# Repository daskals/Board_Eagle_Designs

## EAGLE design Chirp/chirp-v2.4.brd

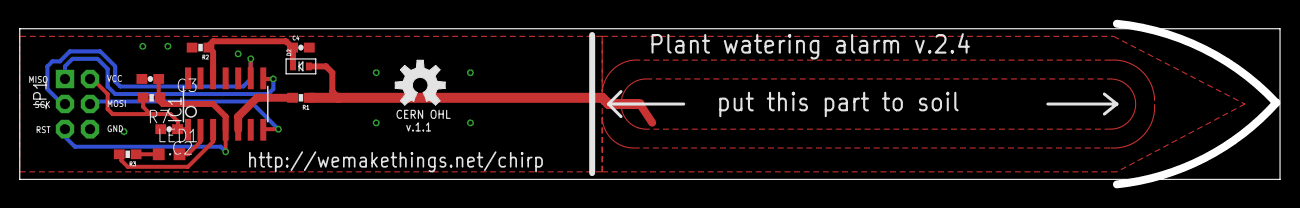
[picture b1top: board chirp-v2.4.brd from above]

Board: 2 copper layers, 127.5 x 16.3 mm, 11 parts (0 on the bottom side), 12 nets.

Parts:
C2, C3: 100nF; 0603-CAP
C4: 1uF; 0603-CAP
D2: DIODE-SCHOTTKY_; SOD-523
IC1: TINY24/44/84-SSU; SOIC14
JP1: AVR_SPI_PRG_6NS; 2X3-NS
LED1: CHIPLED_0805
R1, R7: 10K; 0603-RES
R2: 510K; 0603-RES
R3: 100R; 0603-RES

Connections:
CAPACITANCE_V: C4.1, D2.K, IC1.12, R2.1
CLK_OUT: IC1.5, R1.2
GND: C2.2, C3.2, C4.2, IC1.14, JP1.6, R2.2
LED_A: IC1.3, R3.2
LED_K: IC1.2, LED1.C
MISO: IC1.8, JP1.1
MOSI: IC1.7, JP1.4
unnamed: LED1.A, R3.1
RESET: C3.1, IC1.4, JP1.5, R7.1
SCK: IC1.9, JP1.3
VCC: C2.1, IC1.1, JP1.2, R7.2
V_CAP: D2.A, R1.1

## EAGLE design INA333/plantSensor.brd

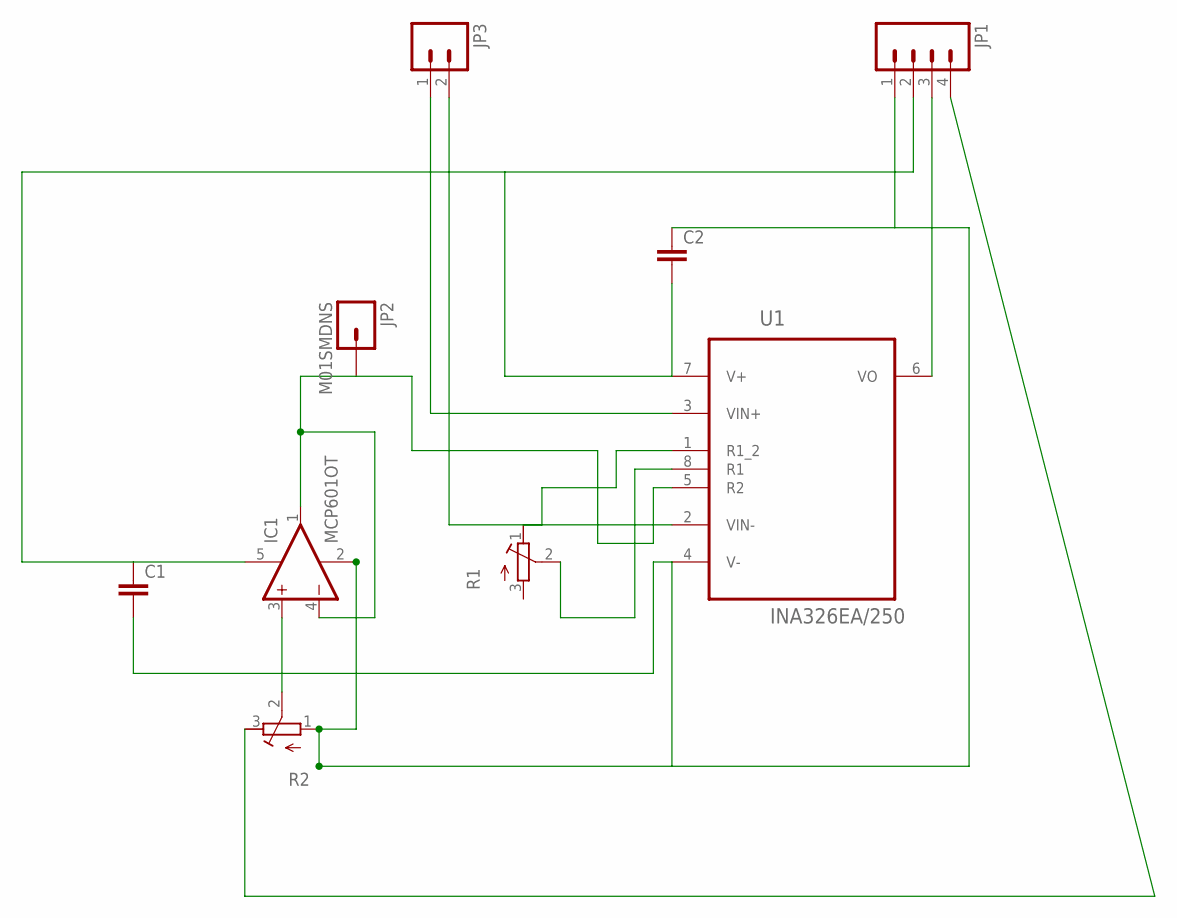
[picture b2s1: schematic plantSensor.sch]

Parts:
C1, C2: C2.5/4; C2.5-4
IC1: MCP601OT; SOT23-5
JP1: M04PTH; 1X04
JP2: M01SMDNS; 1X01NS
JP3: M02PTH; 1X02
R1: R-TRIMM3314G; RTRIM3314G
R2: R-TRIMM3314J; RTRIM3314J
U1: INA326EA/250; SOP65P490X110-8N

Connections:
AA: C1.1, C2.2, IC1.5 (V+), JP1.2, U1.7 (V+)
GND: C1.2, C2.1, IC1.2 (V-), JP1.1, R2.1 (E), U1.4 (V-)
unnamed: JP1.3, U1.6 (VO)
unnamed: IC1.3 (+IN), R2.2 (S)
unnamed: JP3.2, U1.2 (VIN-)
unnamed: JP3.1, U1.3 (VIN+)
unnamed: R1.2 (S), U1.8 (R1)
unnamed: R1.1 (E), U1.1 (R1_2)
unnamed: JP1.4, R2.3 (A)
unnamed: IC1.1 (OUT), IC1.4 (-IN), JP2.1, U1.5 (R2)

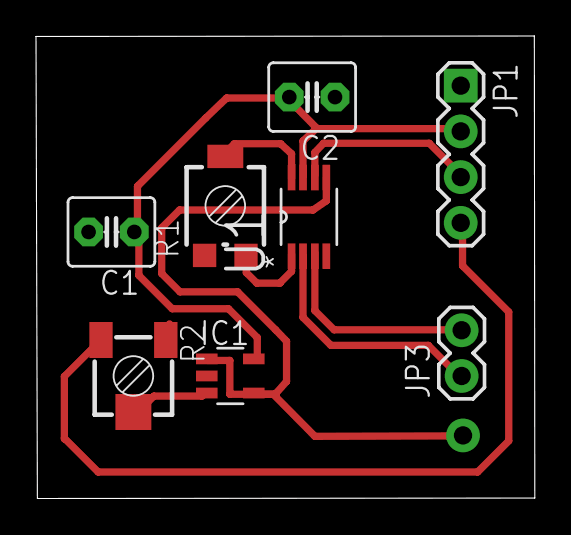
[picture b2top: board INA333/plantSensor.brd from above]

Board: 2 copper layers, 27.7 x 25.7 mm, 9 parts (0 on the bottom side), 10 nets.

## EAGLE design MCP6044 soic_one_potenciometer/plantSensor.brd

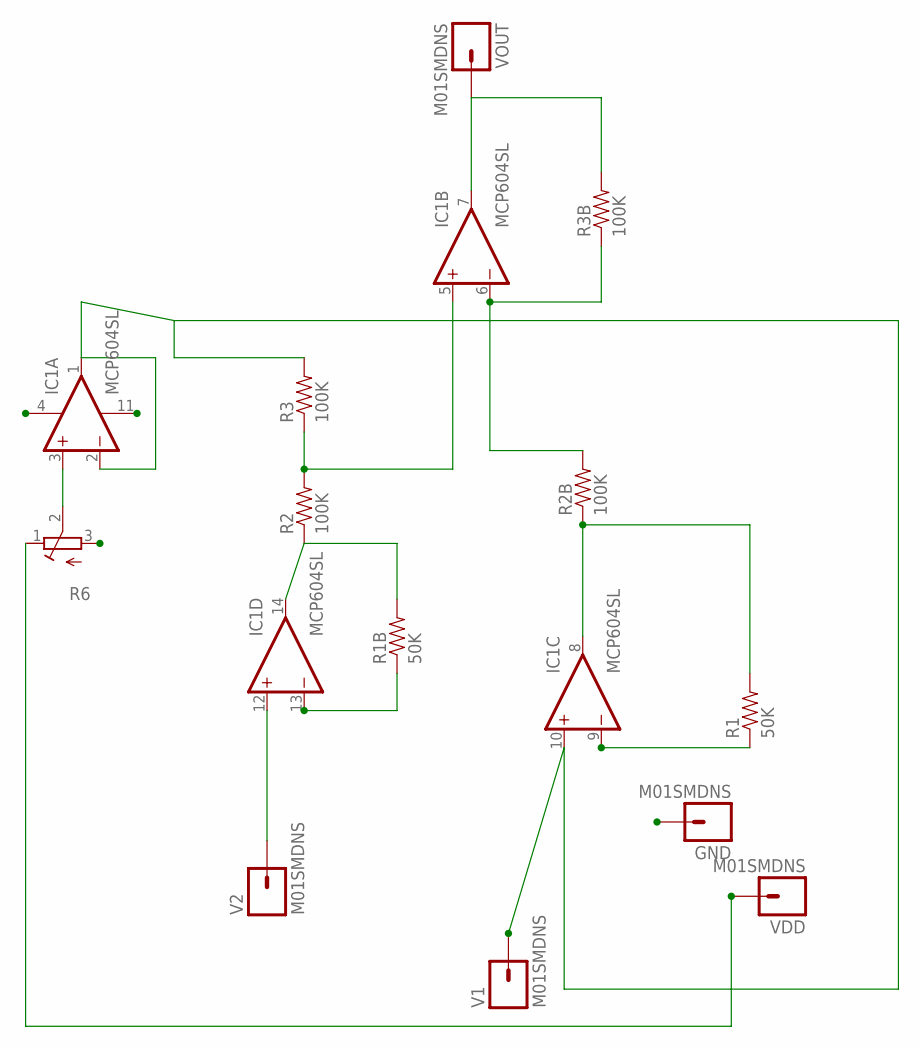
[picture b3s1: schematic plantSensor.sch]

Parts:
GND: M01SMDNS; 1X01NS
IC1: MCP604SL; SO14
R1, R1B: 50K; 0805
R2, R2B, R3, R3B: 100K; 0805
R6: R-TRIMM3314G; RTRIM3314G
V1, V2: M01SMDNS; 1X01NS
VDD: M01SMDNS; 1X01NS
VOUT: M01SMDNS; 1X01NS

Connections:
GND: GND.1, IC1.11 (V-), R6.3 (A)
unnamed: IC1.13 (-IN), R1B.1
unnamed: IC1.12 (+IN), V2.1
unnamed: IC1.3 (+IN), R6.2 (S)
unnamed: IC1.5 (+IN), R2.2, R3.1
unnamed: IC1.9 (-IN), R1.1
unnamed: IC1.8 (OUT), R1.2, R2B.1
unnamed: IC1.14 (OUT), R1B.2, R2.1
unnamed: IC1.6 (-IN), R2B.2, R3B.1
unnamed: IC1.7 (OUT), R3B.2, VOUT.1
VDD: IC1.4 (V+), R6.1 (E), VDD.1
VRF: IC1.1 (OUT), IC1.2 (-IN), IC1.10 (+IN), R3.2, V1.1

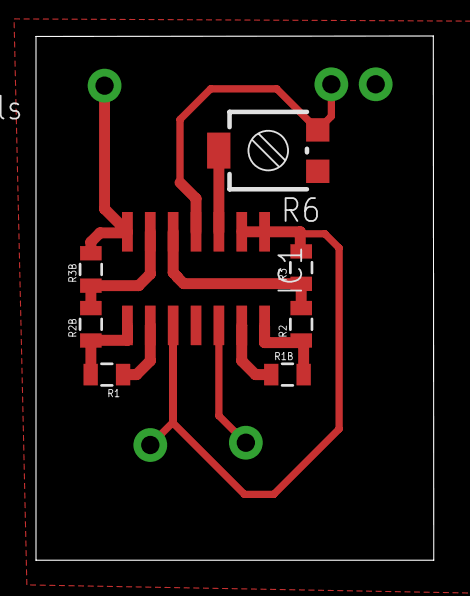
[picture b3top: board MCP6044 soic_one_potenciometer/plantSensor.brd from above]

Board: 2 copper layers, 22.1 x 29.1 mm, 13 parts (0 on the bottom side), 12 nets.

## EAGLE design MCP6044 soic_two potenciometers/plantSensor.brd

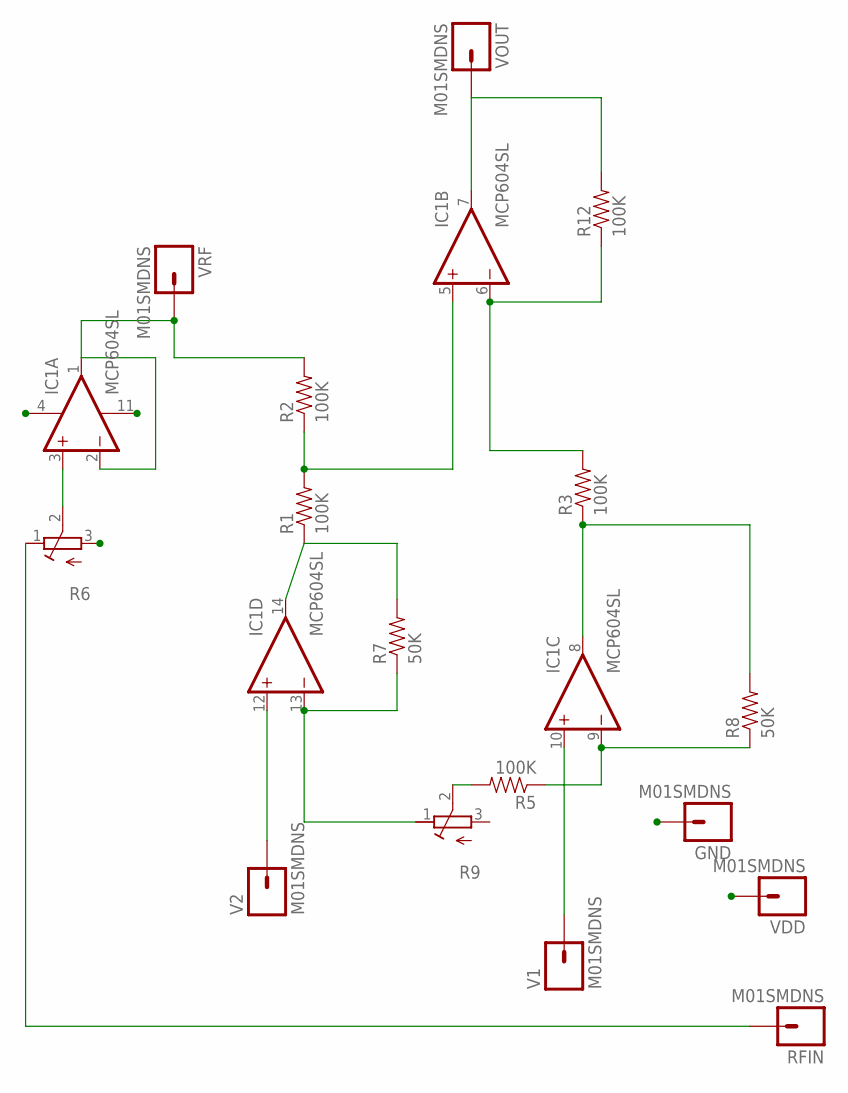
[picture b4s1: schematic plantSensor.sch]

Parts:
GND: M01SMDNS; 1X01NS
IC1: MCP604SL; SO14
R1, R2, R3, R5, R12: 100K; 0805
R6, R9: R-TRIMM3314G; RTRIM3314G
R7, R8: 50K; 0805
RFIN: M01SMDNS; 1X01NS
V1, V2: M01SMDNS; 1X01NS
VDD: M01SMDNS; 1X01NS
VOUT: M01SMDNS; 1X01NS
VRF: M01SMDNS; 1X01NS

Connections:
GND: GND.1, IC1.11 (V-), R6.3 (A)
unnamed: IC1.10 (+IN), V1.1
unnamed: R5.2, R9.2 (S)
unnamed: IC1.13 (-IN), R7.1, R9.1 (E)
unnamed: IC1.12 (+IN), V2.1
unnamed: R6.1 (E), RFIN.1
unnamed: IC1.3 (+IN), R6.2 (S)
unnamed: IC1.5 (+IN), R1.2, R2.1
unnamed: IC1.9 (-IN), R5.1, R8.1
unnamed: IC1.8 (OUT), R3.1, R8.2
unnamed: IC1.14 (OUT), R1.1, R7.2
unnamed: IC1.6 (-IN), R3.2, R12.1
unnamed: IC1.7 (OUT), R12.2, VOUT.1
VDD: IC1.4 (V+), VDD.1
VRF: IC1.1 (OUT), IC1.2 (-IN), R2.2, VRF.1

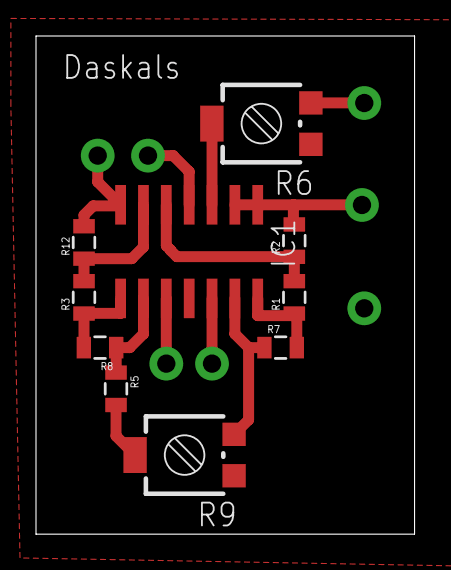
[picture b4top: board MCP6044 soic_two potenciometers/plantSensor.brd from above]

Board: 2 copper layers, 21.0 x 27.7 mm, 17 parts (0 on the bottom side), 15 nets.

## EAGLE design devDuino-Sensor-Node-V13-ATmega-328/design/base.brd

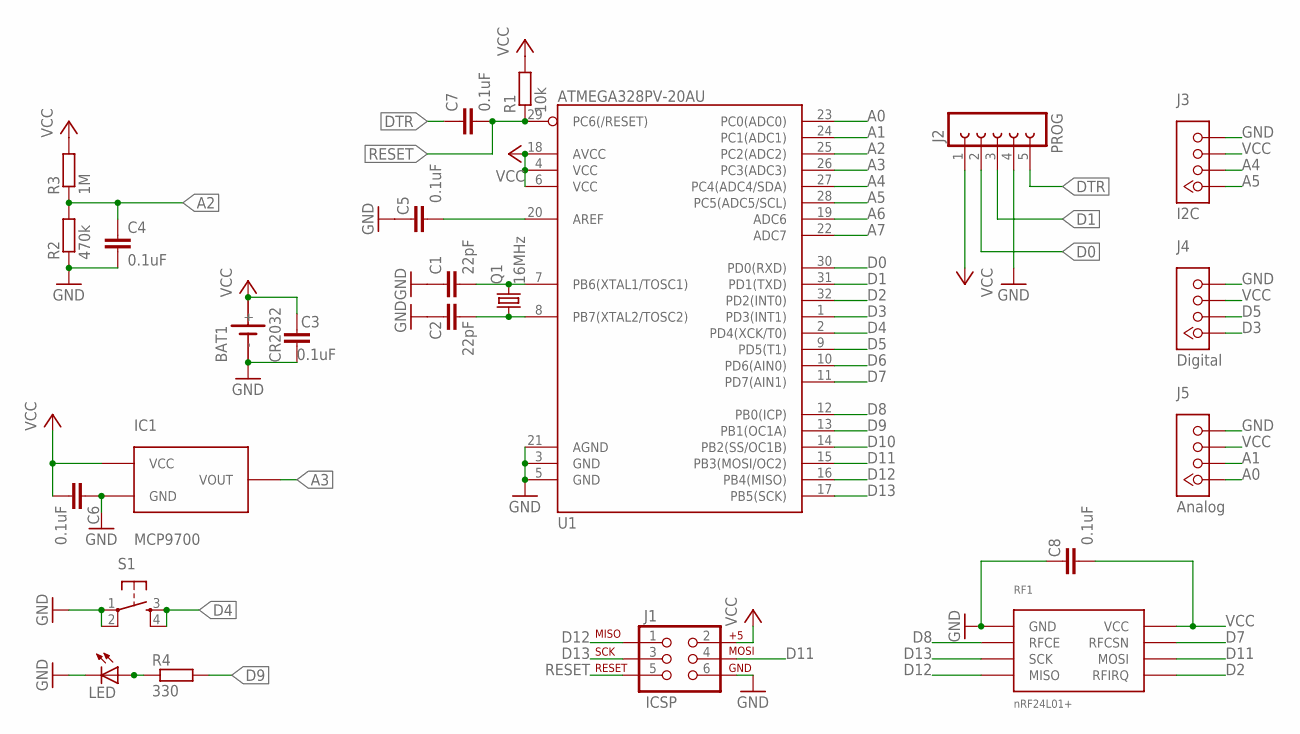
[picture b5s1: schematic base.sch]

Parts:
BAT1: CR2032; SN2032
C1, C2: 22pF; C0805
C3, C4, C5, C6, C7, C8: 0.1uF; C0805
IC1: MCP9700; SOT23
J1: ICSP; 2X3-NS
J3: I2C; TWIG-4P-2.0
J4: Digital; TWIG-4P-2.0
J5: Analog; TWIG-4P-2.0
LED: LEDCHIP-LED0805; CHIP-LED0805
PROG: J2; FE05-1
Q1: 16MHz; CTS406
R1: 10k; R0805
R2: 470k; R0805
R3: 1M; R0805
R4: 330; R0805
RF1: nRF24L01+; 2X4-2.54MM
S1: TAC_SWITCHPTH; TACTILE-PTH
U1: ATMEGA328PV-20AU; TQFP32-08

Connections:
A0: J5.P$1, U1.23 (PC0(ADC0))
A1: J5.P$2, U1.24 (PC1(ADC1))
A2: C4.1, R2.2, R3.1, U1.25 (PC2(ADC2))
A3: IC1.VOUT, U1.26 (PC3(ADC3))
A4: J3.P$2, U1.27 (PC4(ADC4/SDA))
A5: J3.P$1, U1.28 (PC5(ADC5/SCL))
A6: U1.19 (ADC6)
A7: U1.22 (ADC7)
D0: PROG.2, U1.30 (PD0(RXD))
D1: PROG.3, U1.31 (PD1(TXD))
D2: RF1.P$8 (RFIRQ), U1.32 (PD2(INT0))
D3: J4.P$1, U1.1 (PD3(INT1))
D4: S1.3, S1.4, U1.2 (PD4(XCK/T0))
D5: J4.P$2, U1.9 (PD5(T1))
D6: U1.10 (PD6(AIN0))
D7: RF1.P$4 (RFCSN), U1.11 (PD7(AIN1))
D8: RF1.P$3 (RFCE), U1.12 (PB0(ICP))
D9: R4.2, U1.13 (PB1(OC1A))
D10: U1.14 (PB2(SS/OC1B))
D11: J1.4, RF1.P$6 (MOSI), U1.15 (PB3(MOSI/OC2))
D12: J1.1, RF1.P$7 (MISO), U1.16 (PB4(MISO))
D13: J1.3, RF1.P$5 (SCK), U1.17 (PB5(SCK))
DTR: C7.1, PROG.5
GND: BAT1.-, C1.1, C2.1, C3.1, C4.2, C5.2, C6.1, C8.2, IC1.GND, J1.6, J3.P$4, J4.P$4, J5.P$4, LED.C, PROG.4, R2.1, RF1.P$1 (GND), S1.1, S1.2, U1.3 (GND), U1.5 (GND), U1.21 (AGND)
unnamed: C1.2, Q1.3 (2), U1.7 (PB6(XTAL1/TOSC1))
unnamed: C2.2, Q1.1, U1.8 (PB7(XTAL2/TOSC2))
unnamed: C5.1, U1.20 (AREF)
unnamed: LED.A, R4.1
RESET: C7.2, J1.5, R1.1, U1.29 (PC6(/RESET))
VCC: BAT1.+, C3.2, C6.2, C8.1, IC1.VDD (VCC), J1.2, J3.P$3, J4.P$3, J5.P$3, PROG.1, R1.2, R3.2, RF1.P$2 (VCC), U1.4 (VCC), U1.6 (VCC), U1.18 (AVCC)

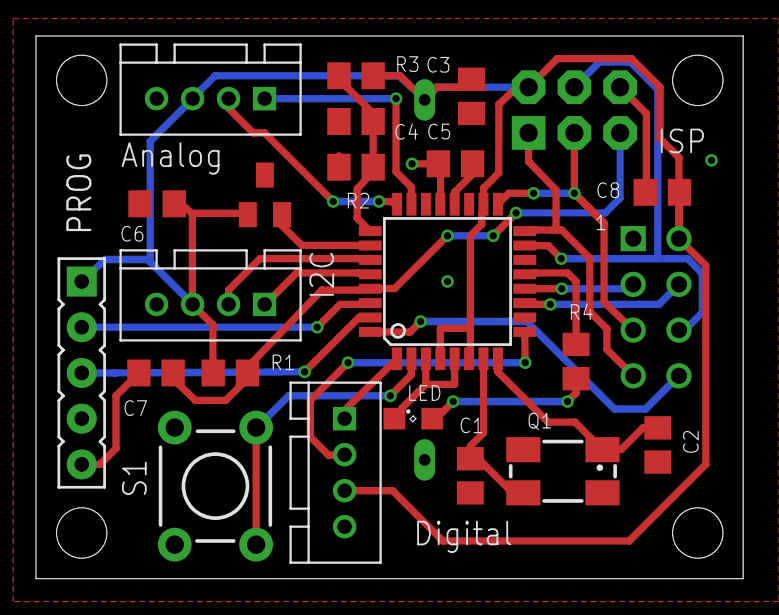
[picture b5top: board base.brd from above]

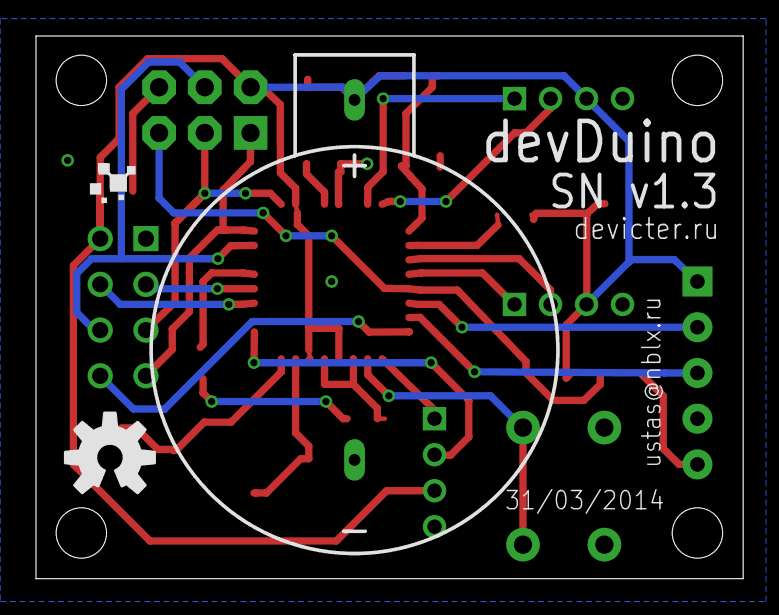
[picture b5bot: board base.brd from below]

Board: 2 copper layers, 39.3 x 30.2 mm, 25 parts (2 on the bottom side), 26 nets.

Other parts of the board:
E$1: OSHW-LOGO-M

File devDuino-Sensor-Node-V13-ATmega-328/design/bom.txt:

Assembly variant: 

Part Value            Device          Package      Description               
BAT1 CR2032           SN2032          SN2032       LI BATTERY                
C1   22pF             C-EUC0805       C0805        CAPACITOR, European symbol
C2   22pF             C-EUC0805       C0805        CAPACITOR, European symbol
C3   0.1uF            C-EUC0805       C0805        CAPACITOR, European symbol
C4   0.1uF            C-EUC0805       C0805        CAPACITOR, European symbol
C5   0.1uF            C-EUC0805       C0805        CAPACITOR, European symbol
C6   0.1uF            C-EUC0805       C0805        CAPACITOR, European symbol
C7   0.1uF            C-EUC0805       C0805        CAPACITOR, European symbol
C8   0.1uF            C-EUC0805       C0805        CAPACITOR, European symbol
IC1  MCP9700          MCP9700         SOT23                                  
J1   ICSP             AVR_SPI_PRG_6NS 2X3-NS       AVR ISP 6 Pin             
J3   I2C              TWIG-4P-2.0     TWIG-4P-2.0  Groove series                          
J4   Digital          TWIG-4P-2.0     TWIG-4P-2.0  Groove series                          
J5   Analog           TWIG-4P-2.0     TWIG-4P-2.0  Groove series                          
LED                   LEDCHIP-LED0805 CHIP-LED0805 LED (RED)                      
PROG J2               FE05-1          FE05-1       FEMALE HEADER             
Q1   16MHz            CRYSTALCTS406   CTS406       CRYSTAL                   
R1   10k              R-EU_R0805      R0805        RESISTOR, European symbol 
R2   470k             R-EU_R0805      R0805        RESISTOR, European symbol 
R3   1M               R-EU_R0805      R0805        RESISTOR, European symbol 
R4   330              R-EU_R0805      R0805        RESISTOR, European symbol 
RF1  nRF24L01+        NRF24L01        2X4-2.54MM                             
S1                    TAC_SWITCHPTH   TACTILE-PTH  Momentary Switch          
U1   ATMEGA328PV-20AU ATMEGA328_SMT   TQFP32-08    32-Pin Atmega328 part

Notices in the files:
Chirp/chirp-v2.4.brd:
CERN OHL
parts and their libraries:
SparkFun-Connectors: Licensing: CC v3.0 Share-Alike You are welcome to use this library for commercial purposes.
